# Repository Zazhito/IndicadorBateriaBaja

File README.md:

# IndicadorBateriaBaja
 Circuito Analogo para indicar cuando la tension de una bateria o fuente ha decaido por debajo de un umbral establecido

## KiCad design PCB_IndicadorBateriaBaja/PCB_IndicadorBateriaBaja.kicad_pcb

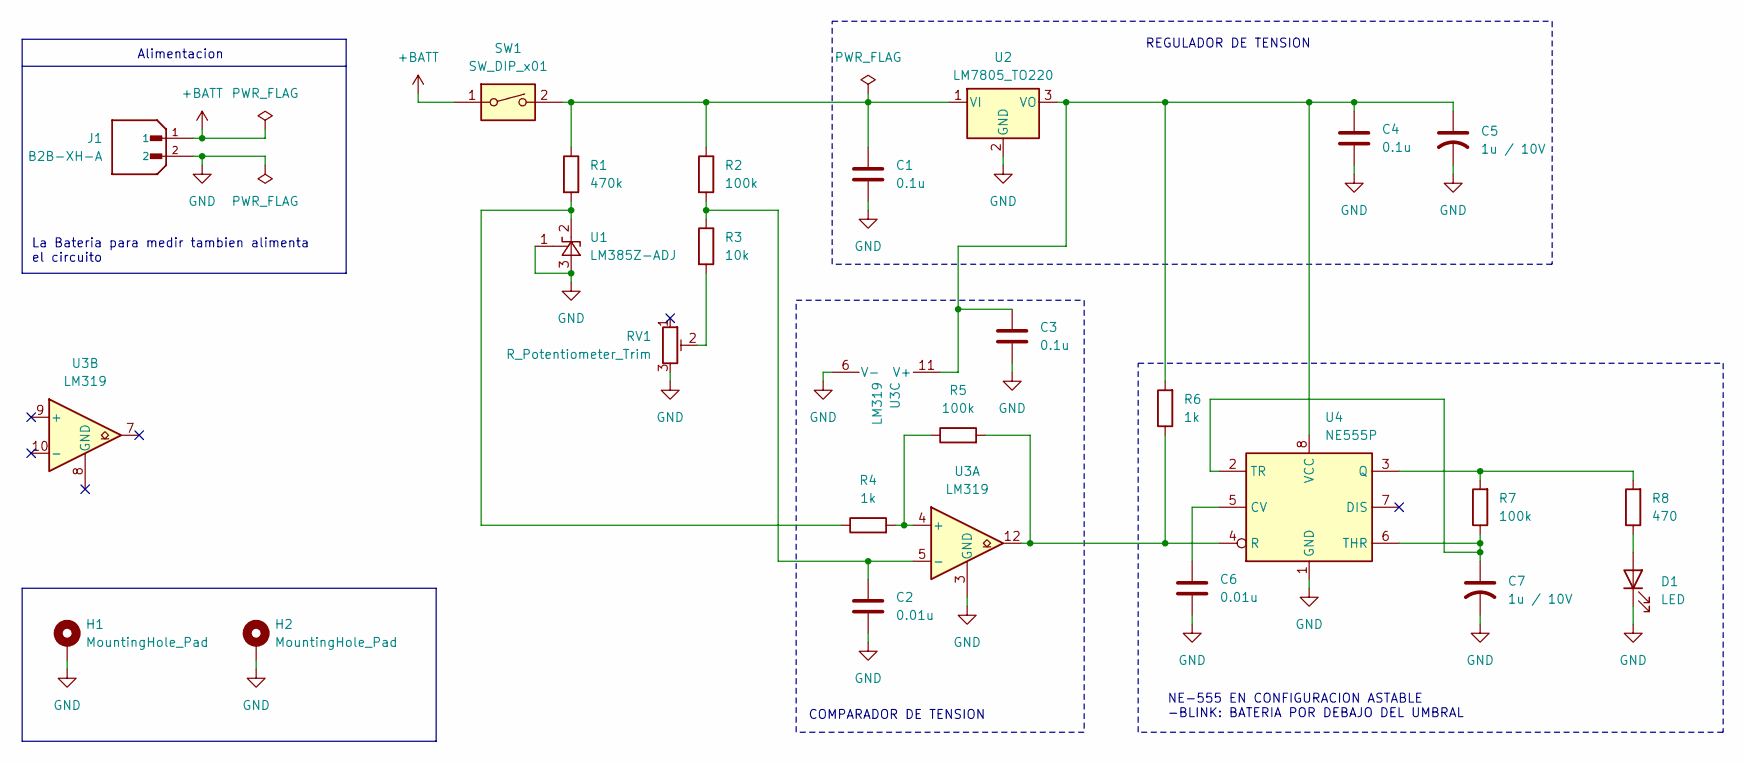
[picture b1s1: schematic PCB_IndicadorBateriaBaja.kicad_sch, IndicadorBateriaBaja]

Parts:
C1, C3, C4: 0.1u; C_0805_2012Metric_Pad1.18x1.45mm_HandSolder
C2, C6: 0.01u; C_0805_2012Metric_Pad1.18x1.45mm_HandSolder
C5: 1u / 10V; C_1206_3216Metric_Pad1.33x1.80mm_HandSolder
C7: 1u / 10V; CP_EIA-1608-08_AVX-J_HandSolder
D1: LED; LED_D3.0mm
H1, H2: MountingHole_Pad; MountingHole_3mm_Pad
J1: B2B-XH-A; JST_B2B-XH-A; PARTREV N/A
R1: 470k; R_0805_2012Metric_Pad1.20x1.40mm_HandSolder
R2, R5, R7: 100k; R_0805_2012Metric_Pad1.20x1.40mm_HandSolder
R3: 10k; R_0805_2012Metric_Pad1.20x1.40mm_HandSolder
R4, R6: 1k; R_0805_2012Metric_Pad1.20x1.40mm_HandSolder
R8: 470; R_0805_2012Metric_Pad1.20x1.40mm_HandSolder
RV1: R_Potentiometer_Trim; Potentiometer_Bourns_3266Y_Vertical
SW1: SW_DIP_x01; SW_DIP_SPSTx01_Slide_6.7x4.1mm_W7.62mm_P2.54mm_LowProfile
U1: LM385Z-ADJ; TO-92_Inline
U2: LM7805_TO220; TO-220-3_Vertical
U3: LM319; SOIC-14_3.9x8.7mm_P1.27mm
U4: NE555P; DIP-8_W7.62mm

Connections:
+BATT: J1.1, SW1.1
GND: C1.2, C2.2, C3.2, C4.2, C5.2, C6.2, C7.2, D1.1 (K), H1.1, H2.1, J1.2, RV1.3, U1.1 (FB), U1.3 (A), U2.2 (GND), U3.3 (GND), U3.6 (V-), U4.1 (GND)
unnamed: D1.2 (A), R8.1
unnamed: R3.2, RV1.2
unnamed: R1.2, R4.1, U1.2 (K)
unnamed: C1.1, R1.1, R2.1, SW1.2, U2.1 (VI)
unnamed: C3.1, C4.1, C5.1, R6.2, U2.3 (VO), U3.11 (V+), U4.8 (VCC)
unnamed: R4.2, R5.1, U3.4 (+)
unnamed: C2.1, R2.2, R3.1, U3.5 (-)
unnamed: C6.1, U4.5 (CV)
unnamed: R7.2, R8.2, U4.3 (Q)
unnamed: R5.2, R6.1, U3.12, U4.4 (R)
unnamed: C7.1, R7.1, U4.2 (TR), U4.6 (THR)

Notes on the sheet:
Alimentacion
La Bateria para medir tambien alimenta el circuito
REGULADOR DE TENSION
NE-555 EN CONFIGURACION ASTABLE -BLINK: BATERIA POR DEBAJO DEL UMBRAL
COMPARADOR DE TENSION

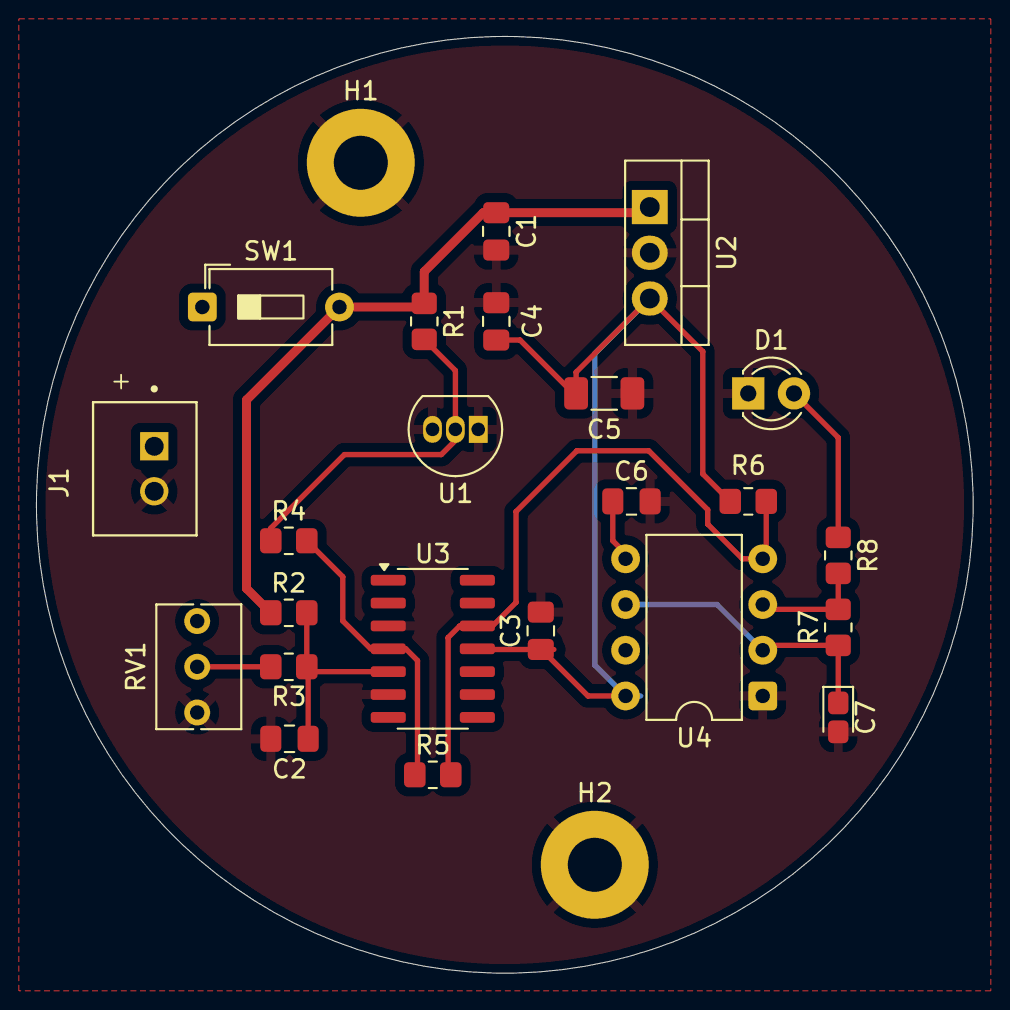
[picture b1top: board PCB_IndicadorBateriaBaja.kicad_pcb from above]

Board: 2 copper layers, 52.0 x 52.0 mm, 25 parts (0 on the bottom side), 13 nets.

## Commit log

2025-04-27 vFinal
    Proyecto Finalizado
